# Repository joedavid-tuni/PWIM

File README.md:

## ELECTRONIC CONTROL OF HYRDRAULIC SYSTEMS

## Description of the Task

As mobile equipment becomes more technologically sophisticated, the need for electronic control of
hydraulic systems is growing.

Electronic components have become more reliable and rugged. They can now withstand the harsh
environmental conditions required for mobile equipment applications. Sophisticated electronic
controllers normally supply only low power control signals.

The goal of the project is to build an electronic driver circuit that compensates the stiction and
hysteresis of a hydraulic valve that makes their behaviour seem erratic and unpredictable. Once we
get over these issues we move on to implement a current sensing mechanism by which the current
in the solenoid circuit is prevented from fluctuating due to varying resistance from varying
temperatures of the coil. We as such are not interested in the position of the spool at any given
point in time but rather only to regulate the current.

## Table of Contents

- Terms of Reference
- Abstract
- Acknowledgement
- 1. Introduction
   - 1.1 Hydraulic Valve
      - 1.1.1 Introduction
      - 1.1.2 Working Principle
      - 1.1.3 Solenoid
      - 1.1.4 Characteristics of Solenoid Coil
   - 1.2 Methods for Proportional Control
      - 1.2.1 Using a potentiometer in Series with the Solenoid
      - 1.2.2 Pulse Width Modulation
      - 1.2.3 Problems associated with Proportional Control of Solenoids
   - 1.3 Solutions to Problems associated with Proportional Control – The Concept of Dither
      - 1.3.1 High frequency PWM
      - 1.3.2 Low frequency PWM
      - 1.3.3 Superimposing Low Frequency Dither on High Frequency Signal
- 2. Current Sensing
   - 2.1 INA219
   - 2.2 PID Algorithm
- 3. Project Work
   - 3.1 Major Hardware Components
   - 3.2 Software
      - 3.2.1 Simulation
      - 3.2.2 Programming IDE
      - 3.2.3 PCB Design Software
   - 3.3 Project Implementation
      - 3.3.1 Basic Circuit
      - 3.3.2 Calculating Inductance
      - 3.3.3 Dither
      - 3.3.4 Current Sensing
      - 3.3.5 Making the PCB
- 4. Project Setup
- 5. Conclusion
- 6. Project Resources
- 7. References
- APPENDIX A: I^2 C Communication Protocol
- APPENDIX B: Setting PWM Frequency on Arduino
- APPENDIX C: The PID Algorithm
- APPENDIX D: TROUBLESHOOTING
- Figure 1: Parts of the Hydraulic Valve List of Figures
- Figure 2: Internal cross section of the Hydraulic Valve
- Figure 3: Coil of Solenoid A energized
- Figure 4: Neutral Position of Valve Plunger
- Figure 5: Testing using mechanical override
- Figure 6: Cross-sectional sketch of Solenoid A of hydraulic valve
- Figure 7: Depiction of the magnetic field around solenoid
- Figure 8: Solenoid current characteristics
- Figure 9: Width of pulses at different duty cycles
- Figure 10: Duty cycle with respective current waveform
- Figure 11: A typical hysteresis curve in an electro hydraulic proportional valve
- Figure 12: Dither as a by-product of low frequency PWM
- Figure 13: Low Frequency Dither superimposed on high frequency PWM
- Figure 14: Functional block diagram of commercially available Solenoid Driver
- Figure 15: Dither Generating Circuitry of a commercially available driver
- Figure 16: Software Code for creating Dither
- Figure 17: Functional Block Diagram of INA219 Sensor
- Figure 18: LCD Display used in the project
- Figure 19: Screenshot of Multisim GUI
- Figure 20: Screenshot of Labcenter Proteus GUI
- Figure 21: Screenshot of Arduino IDE GUI
- Figure 22: Screenshot of Autodesk Eagle GUI
- Figure 23: An FET and a freewheeling diode used to drive the solenoid valve.
- Figure 24: Laboratory setup while calculating inductance
- Figure 25: Oscilloscope Screenshot at resonance
- Figure 26: Multisim simulation circuit
- Figure 27: Breadboard schematic
- Figure 28: General Schematic
- Figure 29: Simulated oscilloscope screenshot (Low frequency)
- Figure 30: Project Implementation waveform from the Arduino (Low frequency)
- Figure 31: Simulated oscilloscope screenshot (High frequency)
- Figure 32: Project Implementation waveform from the Arduino (High frequency)
- Figure 33:: Project Implementation of superimposed waveform from the Arduino.
- Figure 34: Breadboard schematic for current sensing
- Figure 35: Project implemented waveform from the Arduino with current sensing incorporated
- Figure 36: Schematic of Printed Circuit Board of Valve Driver Circuit
- Figure 37: Board Layout of Printed Circuit Board of Valve Driver Circuit
- Figure 38: 3D rendered images of designed Printed Circuit Board
- Figure 39: 3D rendered images of designed Printed Circuit Board
- Figure 40: 3D rendered images of designed Printed Circuit Board
- Figure 41: 3D rendered images of designed Printed Circuit Board
- Figure 42: Project Setup

## 1. Introduction

### 1.1 Hydraulic Valve

#### 1.1.1 Introduction

The Hydraulic Valve used for this Project is a bi-directional solenoid valve from BOSCH.

These are designed to perform any of three actions. They direct the flow of fluid in a hydraulic
system in a particular direction. They can halt or initiate the flow of fluid in a system. Directional
valves can also change the direction in which a fluid flows within a circuit. Various directional valves
are incorporated in hydraulic systems to enable proper flow of fluids. Spool valves in particular are
designed to block and allow the flow of fluid within a hydraulic system.

Parts of the Hydraulic Valve (as labelled in Figure 1)

1. 3 port/chamber system with spool guidance
2. Pressure tight solenoid
3. Optimized flow paths
4. Manual override with return spring

#### Figure 1 : Parts of the Hydraulic Valve

#### 1.1.2 Working Principle

#### Figure 2: Internal cross section of the Hydraulic Valve

The valve contains two coils on its either end and together with the valve tube that contains an  armature and a push pin make up what is known as a solenoid.

In the main body of the valve there are two springs that help return the spool when no solenoids are
energized. The lines with the gauges labelled A and B are the work ports that typically connect to a
hydraulic cylinder or a motor.

When Solenoid A of the valve is energized an electromagnetic field is created (Figure1). The field
pulls the armature in towards the centre of the winding which causes the armature to slide easily in
a tube that is internally lubricated with hydraulic oil. The armature moves the push pin and
ultimately the push pin moves the valve spool towards the right and now there will be a flow from
the pump directed to work port B. Likewise when Solenoid B is energized, the spool moves to the
left.

#### Figure 3: Coil of Solenoid A energized

Notice that when Solenoid A is energised the movement of the spool towards the right also causes
the pushpin and armature in Solenoid B is pushed to the right as well.

Also notice that in Figure 2 there is a gap present between the pushpin on the left side of the spool.
When Solenoid A is energized the armature and the push pin gets a running start against the spool
as the gap is closed.

When the solenoid returns to the neutral position after Solenoid A is energized the gap is present
with the Solenoid B. Whichever side of the valve has the pushpin gap has a slight force advantage
when that Solenoid is next energized (Figure 4 ).

#### Figure 4: Neutral Position of Valve Plunger

In order to help with troubleshooting and basic valve testing, the valve is provided with a mechanical
override (Figure 5), A mechanical override is simply a pin on the outside end of the valve tube in the
centre of the solenoid assembly that can be activated with a small screwdriver or hex key. Pushing
on the mechanical override is a simple way to find out if the internal parts of the valve is still free to
move and operating normally.

#### Figure 5: Testing using mechanical override

#### 1.1.3 Solenoid

The hydraulic solenoid valve as mentioned has two solenoids as actuators mounted on either ends
of the valve body. These linear solenoids are electromechanical devices which convert electrical
energy into a linear mechanical motion which is used to control the hydraulic system.
Figure 6 shows a cross sectional sketch of the electromagnetic solenoid hydraulic valve. The
solenoids consist of an electromagnetically inductive coil wound around a movable armature, or
plunger. The coil is shaped such that the armature can be moved in and out of its centre, altering the
coil’s inductance. The plunger provides mechanical force to activate the control mechanism, for
example opening and closing of a valve.

#### Figure 6: Cross-sectional sketch of Solenoid A of hydraulic valve

#### 1.1.4 Characteristics of Solenoid Coil

A main electrical characteristic of a solenoid is that of an inductor that opposes any change in
current. This characteristic is why current does not immediately reach a maximum level when a
solenoid is energized. Instead, the current rises at a steady rate until it is limited by the DC resistance
of the solenoid.

#### Figure 7: Depiction of the magnetic field around solenoid

An inductor (in this case a solenoid) stores energy in the form of a concentrated magnetic field.
Whenever current is present in a wire or conductor, a magnetic field, however small, is created
around the wire. With the wire wound into a coil, such as in the solenoid, the magnetic field
becomes very concentrated. This electromagnet can control a mechanical valve through an electrical
signal.

As soon as the solenoid is energized, the current increases, causing the magnetic field to expand
until it becomes strong enough to move the armature and the corresponding solenoid current is
known as IPEAK.

#### Figure 8: Solenoid current characteristics

The armature movement increases the concentration of the magnetic field as the armature’s own
magnetic mass moves farther into the magnetic field. Remember, a magnetic field changing in the
same direction of the current creating it induces an opposing voltage into the windings. Because the
magnetic field quickly expands when the armature strokes, the field causes a brief reduction in the
current through the solenoid windings till a minimum known as IVALLEY (Figure 8). Notice the
prominent dip in the rising portion of the current waveform.

After the armature strokes, the current continues on its normal upward path to its maximum level. A
typical current waveform in shown in Figure 8.

### 1.2 Methods for Proportional Control

When voltage is applied to a valve coil, the current flowing through it creates a magnetic field which
provides the force to shift the valve’s spool. The input voltage divided by the resistance of the coil
equals the current draw. This is very straightforward when used with on/off valves, but proportional
valves are only useful if the spool position can be precisely controlled by varying the input current.

#### 1.2.1 Using a potentiometer in Series with the Solenoid

A simple potentiometer can be used to vary the resistance, which then varies the input current. This
is an inefficient method of control, and is not practical when high currents are required. Also, when
an infinitely variable DC signal is used to operate a proportional valve solenoid, the output transistor
functions like a variable resistor. It drops the power supply voltage down to the level required by the
solenoid coil at a particular time. The full coil current, which may be several amps, needs to pass
through this output transistor. The result is that the transistor builds up heat which requires a large
heat sink to dissipate.

#### 1.2.2 Pulse Width Modulation

Pulse Width Modulation (PWM) is a control technique which can overcome the problems described
above. With PWM, the output transistor is used as an on/off switch, feeding the solenoid coil with a
series of on/off pulses at a constant voltage. The pulses are set at a constant frequency, typically 400
to 5000+ Hz. The signal level is determined by varying the duration of the “on” pulses relative to the
“off” pulses.

The advantage of this technique is that during the “off” pulse, the output transistor is not passing
any current, and during the “on” pulse, there is virtually no voltage drop across the transistor and
therefore very little heat is created. In practice, there will be a small voltage drop across the
transistor during the “on” pulses, and it takes a finite amount of time to switch on and off, so a small
amount of heat is created. However, the amount of heat is much smaller than would be produced by
a conventional DC output signal.

PWM has become the standard for all valve amplifiers in order to reduce amplifier size and power
waste. No modifications are required to the valve solenoid in order to use this technique.

PWM is an efficient way to control current to a proportional valve coil. It allows the use of
electronics for current regulation, dither, ramping, short circuit protection, and the elimination of
deadband.

**How PWM Works**

A PWM signal is not constant, it is on for a period of time and off for a period of time (see Figure 9 ).

#### Figure 9: Width of pulses at different duty cycles

The duty cycle “D” refers to the “on” portion of the cycle. The duty cycle can be anywhere from 0
(signal always off) to 1 (signal always on). A 50% “D” results in a perfect square wave.

Inductance is the characteristic of a circuit that opposes the starting, stopping or changing of current
flow. Inductance in an electrical system is similar to inertia in a mechanical system. Its effect is to
introduce a time lag into the duty cycle wave form. In theory, the wave form is perfectly rectangular,
rising immediately when current is applied, and falling immediately when current is withdrawn.
Because of the effects of inductance, the actual wave form rises and falls more gradually (see Figure
10 ).

#### Figure 10: Duty cycle with respective current waveform

At 25% signal, “D” is shorter than the time it takes the current to reach its maximum value. This
results in reduced current output to the valve coil, and therefore a reduced hydraulic output from
the valve. If the PWM frequency is low enough, the current will fall to zero during the off time. This
is described as “discontinuous current.”

#### 1.2.3 Problems associated with Proportional Control of Solenoids

There are two major problems that are associated with basic proportional control of solenoid.

1. Stiction

Stiction keeps the valve spool from moving when input signal changes are small. When the signal
finally becomes large enough to initiate movement, the spool will tend to overshoot the position
required for accurate control.

2. Hysteresis

#### Figure 11: A typical hysteresis curve in an electro hydraulic proportional valve

The spool movement in a proportional valve has to overcome some amount of spring force as well
as static friction when the input signal is applied. These forces produce an effect known as
hysteresis. Additionally, the solenoid has to overcome the magnetic hysteresis due to the cyclic
magnetization and demagnetization of the solenoid core. The spool movement in response to the
increasing input signal is not the same as the spool movement created in response to the decreasing
input signal. Hysteresis as shown in the figure above is defined as the difference in the spool position
produced by a particular input signal when it is increasing and then decreasing.

Stiction and hysteresis can make the behaviour of a hydraulic proportional valve seem erratic and
unpredictable. In the following sections, we will see how to overcome these problems.

### 1.3 Solutions to Problems associated with Proportional Control – The Concept of Dither

Dither is a rapid, small movement of the spool around the desired position. It is intended to keep the
spool moving to avoid stiction and average-out hysteresis. Dither amplitude must be **large enough
and the frequency slow enough for the spool to respond, and yet amplitude small and frequency
fast enough to avoid creating a noticeable pulsation in the hydraulic output of the valve.** Dither is
caused by coil current “ripples”—current variations around the desired control signal value. Due to
inertia, the valve spool will follow low frequency ripples better than it will follow high frequency
ripples. The amplitude of the ripples determines if, or how far, the spool will move at a given
frequency.

#### 1.3.1 High frequency PWM

The solenoid valves are very often operated by means of PWM signals at a frequency that is high for
the solenoid valve, for example at l KHZ, in the linear or analog range. The armature of the solenoid
valve cannot synchronously follow this high control frequency in mechanical terms and assumes an
intermediate position.

#### 1.3.2 Low frequency PWM

Previously these problems Were solved in that the frequency of the control signal has been reduced
to such an extent, for example between 70 - 300 HZ, that the armature can still just about follow and
in the intermediate position or central position is preferably deflected only minimally. This results in
oscillation of the armature, and of the valve connected thereto, about the intermediate position at
low amplitude which is conventionally called dither oscillation (dither signal). This dither oscillation is
desired in principle since the friction resistances at the moving parts of the solenoid valve may be
reduced thereby.

However, it is very difficult to stipulate an optimally constant dither signal amplitude **since the
dither signal depends on the PWM frequency and on the pulse-duty factor (duty cycle)** and
therefore on the coil current flowing in the solenoid valve. With this method, it is therefore **not
possible for the dither signal to form a constant amplitude since the PWM frequency has to be
continuously adjusted as a function of the stipulated desired current value and in the process the
amplitude and the frequency of the dither signal change accordingly.**

#### Figure 12: Dither as a by-product of low frequency PWM

#### 1.3.3 Superimposing Low Frequency Dither on High Frequency Signal

A further solution for said problems consists in a low-frequency dither signal being superimposed on
the high frequency of the PWM signal by amplitude modulation. This allows the user to
**independently control** amplitude and frequency of the **solenoid current** and the **dither**. The dither
will therefore be constant for any current level, and its frequency and amplitude can be set by the
user to optimize the function of the particular hydraulic valve. This will be necessary as different
valves from different manufacturers would have different spool dynamics (inertia due to different
size, for example).

#### Figure 13: Low Frequency Dither superimposed on high frequency PWM

The dither is specified by its frequency (Hz) and peak-to-peak current. The dither amplitude is usually
adjustable from 0 to 10% of the rated maximum current of the solenoid.

It is to note that, if the dither frequency is in the range of the control frequency, undesirable low-
frequency beating of the magnetic current can occur. Even the hydraulic system may be damaged
thereby. The beating results because the dither frequency cannot be synchronized with the control
frequency.

**Hardware Techniques**

Most solenoid valve drivers make use of a separate dither generating circuitry and combines it with
the main PWM signal using op-amps. The functional block diagram of one such driver is as shown in
the figure below:

#### Figure 14: Functional block diagram of commercially available Solenoid Driver

A dither generating circuit of a commercially available solenoid driver is shown below. This is capable
of generating triangular and square wave dither.

#### Figure 15: Dither Generating Circuitry of a commercially available driver

Working principle:

The dither generator consists of a comparator stage (A1A), amplitude limiting stages (A1C/D2 AND
A1D/D1) and an integrating amplifier stage (A1B). In the beginning, A1A will attempt to go to
positive or negative saturation. However, the peak voltage will be restricted by D1/A1D or D2/A1C.
A1B ramps up or down, as whatever the case maybe, until the output voltage is sufficient to cause
the feedback voltage at the comparator (through voltage divider R8, R11) to change polarity. At this
point, the polarity of A1A changes and A1B ramp in the opposite direction. This way, the dither
signal is generated.

Solutions of this nature are cost-intensive.

**Software Technique**

For the context of the project, we focus only on
superimposing the dither on main PWM signal. As
such, the requirements are basic and we do not need
sophisticated electronics for the purpose. All the
hardware needed would be the basic hardware for
the PWM switching of the solenoid and the dither can
be implemented without using the dither circuitry buy
by rather manipulating the switching hardware
through the software. This section is a description of
how it is done.

#### Figure 16: Software Code for creating Dither

Using software, the microcontroller is programmed so that the duty cycle of the PWM is periodically
oscillated about its set setpoint, by the dither amplitude which in “duty-cycle language” is in effect a
small finite amount of pulse-duty factor. This in effect causes an extended and thereafter a
shortened PWM signal cyclically which emulates dither. This way, the pulse-duty factor is changed
by the desired amplitude of the dither signal exactly every consequent cycle.

A constant amplitude for the dither signal may advantageously be formed thereby, so the armature
of the solenoid valve always oscillates about its central position with identical excursions, without
the control frequency of the PWM signal being able to have an adverse effect. The resulting reduced
friction resistance therefore allows the position of the armature to be advantageously adjusted and
controlled much more accurately as discussed earlier

The low frequency of the dither signal means that the oscillation of the solenoid valve armature can
be individually adjusted to the type of solenoid valve being used, so, compared with the known
hardware solution, a high level of flexibility results because the adaptation to other types of solenoid
valve can take place by way of a simple calibration process by changing a value in the code that the
microcontroller uses to generate the dither. It is also cost efficient in terms of the components used
as the dither circuitry is now replaced by software code.

## 2. Current Sensing

As mentioned in the previous section, the armature of a solenoid provides a mechanical force to
activate the control mechanism. The force applied to the armature is proportional to the coil’s
change in inductance with respect to the armature’s change in position. The electromagnetic force
of a solenoid directly relates to the current. Traditionally, a voltage drive powers the solenoid coils;
Therefore, the coil consumes a continuous power. A negative effect of this power consumption is
the heating of the coil. The coil temperature is a result of many factors: ambient temperature, self-
heating due to the coil’s power consumption (V × I), heating induced by the contact system, and
other heat sources such as components in the vicinity of the relay. Due to coil heating, the coil
resistance increases. The resistance at elevated temperature is expressed by Equation:

where

- RCoil_20°C is the 20°C value for resistance
- kR_T is the thermal coefficient of copper (= 0.00404 per °C) (1)

Typically given in the datasheet of a solenoid coil, RCoil_20°C can calculate the worst-case coil
resistance at high temperatures.

To compensate for temperature induced changes, we have to implement some sort of current
sensing algorithm which essentially is a current feedback. This allows the solenoid current to be
proportional to the input signal voltage, and independent of the solenoid resistance. Power supply
voltage must be sufficient to overcome the increased or decreased resistance

### 2.1 INA219

The current sensor used for the project is the INA219.

The two analog inputs to the INA219, IN+ and IN–, connect to a shunt resistor in the bus of interest.
The INA219 is typically powered by a separate supply from 3 to 5.5 V. The INA219 senses the small
op across the shunt for shunt voltage, and senses the voltage with respect to ground from IN– for
the bus voltage. Figure 13 shows this operation

#### Figure 17: Functional Block Diagram of INA219 Sensor

### 2.2 PID Algorithm

The PID Controller is implemented to achieve the current sensing functionality. See APPENDIX C: The
PID Algorithm to see the details of the PID Algorithm.

The PID algorithm consists of three basic coefficients; proportional, integral and derivative which are
varied to get optimal response. The basic idea behind a PID controller is to read the values from the
current sensor, then compute the desired actuator output by calculating proportional, integral, and
derivative responses and summing those three components to compute the output.

**Proportional Response:** The proportional component depends only on the difference between the
set point and the process variable. This difference is referred to as the Error term. The proportional
gain (Kp) determines the ratio of output response to the error signal. Increasing the proportional
gain will increase the speed of the control system response. However, if the proportional gain is too
large, the process variable will begin to oscillate. If Kp is increased further, the oscillations will
become larger and the system will become unstable and may even oscillate out of control.

**Integral Response:** The integral component sums the error term over time. The result is that even a
small error term will cause the integral component to increase slowly. The integral response will
continually increase over time unless the error is zero, so the effect is to drive the Steady-State error
to zero. Steady-State error is the final difference between the process variable and set point. A
phenomenon called integral windup results when integral action saturates a controller without the
controller driving the error signal toward zero.

**Derivative Response:** The derivative component causes the output to decrease if the process
variable is increasing rapidly. The derivative response is proportional to the rate of change of the
process variable. Increasing the derivative time (Td) parameter will cause the control system to react
more strongly to changes in the error term and will increase the speed of the overall control system
response. Most practical control systems use very small derivative time (Td), because the Derivative
Response is highly sensitive to noise in the process variable signal. If the sensor feedback signal is
noisy or if the control loop rate is too slow, the derivative response can make the control system
unstable

**Tuning**

The method used for tuning the PID Controller in this project is the “trial and error” method.

In this method, the I and D terms are set to zero first and the proportional gain is increased until the
output of the loop oscillates. As one increases the proportional gain, the system becomes faster, but
care must be taken not make the system unstable.

Once P has been set to obtain a desired fast response, the integral term is increased to stop the
oscillations. The integral term reduces the steady state error, but increases overshoot. Some amount
of overshoot is always necessary for a fast system so that it could respond to changes immediately.
The integral term is tweaked to achieve a minimal steady state error.

Once the P and I have been set to get the desired fast control system with minimal steady state
error, the derivative term is increased until the loop is acceptably quick to its set point. Increasing
derivative term decreases overshoot and yields higher gain with stability but would cause the system
to be highly sensitive to noise.

## 3. Project Work

### 3.1 Major Hardware Components

**Arduino**

The Arduino Uno is a microcontroller board based on the
ATmega328. Arduino is an open-source, prototyping
platform. The Arduino Uno has 14 digital input/output
pins (of which 6 can be used as PWM outputs), 6 analog
inputs, a 16 MHz crystal oscillator, a USB connection, a
power jack, an ICSP header, and a reset button. It
contains everything needed to support the
microcontroller; simply connect it to a computer with a
USB cable or power it with a AC-to-DC adapter or battery
to get started.

Features of the Arduino UNO:

- Microcontroller: ATmega328
- Operating Voltage: 5V
- Input Voltage (recommended): 7-12V
- Input Voltage (limits): 6-20V
- Digital I/O Pins: 14 (of which 6 provide PWM output)
- Analog Input Pins: 6
- DC Current per I/O Pin: 40 mA
- DC Current for 3.3V Pin: 50 mA
- Flash Memory: 32 KB of which 0.5 KB used by bootloader
- SRAM: 2 KB (ATmega328)
- EEPROM: 1 KB (ATmega328)

## • Clock Speed: 16 MHz

We use the Arduino to create the appropriate PWM signals for controlling the voltage to the
solenoid and to implement the algorithm for current sensing.

**Bidirectional Hydraulic Vale**

Manufacturer: Bosch Rexroth (BRH)

Part No.: 0810091203

Solenoid Specs:

Rating: 24V, 1.4A

**Power Supply**

Specs:

Rating: 24V,2.5A

**INA219, Bidirectional Current/Power Monitor with I2C Interface**

The INA219 is current shunt and power monitor with and I^2 C
interface. This along with the fact that it could be wired on the high
side were the prime reasons the device was selected to be used with
the I2C compatible Arduino.

The device is capable of monitoring both shunt voltage and the bus
supply voltage. The device uses a 3-5V supply, drawing a maximum of 1 mA of supply current and
operates from -40°C to 125°C.

**16x4 Liquid Crystal Display.**

A 16x4 LCD Display is used to display the circuit parameters such as duty cycle, current, etc. real
time.

The parameters on Display are:

Line 1: Duty cycle (Range: 0- 100 , from setpoint) Voltage: Voltage of the Solenoid Circuit
Line 2: I1 : Current sensed by the I2: Expected Current from duty cycle
current sensor (Feedback for PID)
Line 3: Power: VI Power Dissipated in the Solenoid Circuit
Line 4: PID constants (Kp, Ki, Kd)

#### Figure 18: LCD Display used in the project

**Other Electrical Components**

```
Device Part No. Rating Quantity Remarks
FET IRF3205PbF VDSS = 55V, ID = 110A (n-Ch) 1 Switching Device
Capacitor .001K 63 100nF 1 Noise Filter
Resistor - 12Ω 1 Current Limiter
Diode 1N5400 3A, Rectifier Diode 1 Freewheeling Diode
Potentiometer/
Joystick
```
- 10KΩ 1 Input to the System

### 3.2 Software

#### 3.2.1 Simulation

National Instruments, Multisim v12.0 (used for simulating electrical characteristics)

#### Figure 19: Screenshot of Multisim GUI

LabCenter, Proteus 8 (used for simulating arduino microcontroller (with code) with electrical circuit)

#### Figure 20: Screenshot of Labcenter Proteus GUI

#### 3.2.2 Programming IDE

##### ARDUINO IDE

#### Figure 21: Screenshot of Arduino IDE GUI

#### 3.2.3 PCB Design Software

#### Figure 22: Screenshot of Autodesk Eagle GUI

### 3.3 Project Implementation

Before the implementation, the circuit needs to be simulated to study the response of the
circuit beforehand so that time is no wasted during implementation stage. An added benefit would
be familiar results and pre-known reasoning during the implementation phase. As mentioned in the
earlier sections we use MultiSim v12.0 and Proteus 8.0 for simulations. Proteus simulations were
made to study the behaviour while designing the project work and its observations are not recorded
here.

#### 3.3.1 Basic Circuit

Driving a solenoid is a rather simple task with very little need for sophisticated electronics. Still, the
basics of inductive load driving must be taken care of if we are to safely actuate this load. These
requisites are:

- A large enough voltage must be applied across the winding in order to supply a current with
    enough magnitude as to push/pull the piston.
- The switch or power stage must be sized according to the dc current we expect to see
    flowing across the solenoid winding.
- An alternate path must be applied to take care of the flowing current once the switching
    element is disabled.

A normal MOSFET requires around 10V applied to the Base pin to fully turn on. Because driving
anything above 5V with an Arduino requires using a level-shifter or amplifier, we use what is called a
logic-level MOSFET (IRF 3205) for direct integration. A logic-level MOSFET can be turned on with a 5v
“logic level” signal, which can be easily interfaced to the Arduino.

If a normal MOSFET with an amplified input from the Arduino is used, care must be taken not to
exceed the maximum gate-to-source voltages. If the limit is exceeded for even a second, it can
destroy the MOSFET, so care should be taken to work within the voltage limits of the MOSFET. The
maximum voltage that can be applied to the gate pin is listed in the datasheet as the “Gate to Source
Voltage” or “Vgs” —this number is usually between 18vdc and 25vdc.

For the IRF 3205 we the maximum Vgs is 20V, so it is safe as the Arduino cannot prover over 5V with
direct integration.

The typical solenoid driver circuit is a single FET transistor with enough current handling capability to
drive the load (IRF 3205), and a freewheeling diode which is forward biased when the FET is
disabled. When the FET is enabled, it sinks all the current needed to polarize the inductor. When the
transistor is disabled, the current flowing through the inductance must be allowed to decay down to
zero. The freewheeling diode is forward biased taking this current and avoiding damage to the
power FET. Figure 1 9 shows the two possible states a solenoid will experience as it is energized

#### Figure 23: An FET and a freewheeling diode used to drive the solenoid valve.

Note that a H-bridge circuit is not used as it’s not a bistable solenoid where the direction of motion
is according to the magnetic field polarity. Hence the direction of current flow is not relevant and
use of an H-bridge would be an overkill as it would need 4 FETs as opposed to one in this case.

All information required to begin simulations is present except one, the inductance of the solenoid
of the hydraulic valve. This was neither found in the product datasheet nor was available with the
Bosch Customer Service personnel on contacting them. So, a basic test is carried out to approximate
the inductance of the solenoid.

#### 3.3.2 Calculating Inductance

To calculate the inductance, connect the solenoid of the hydraulic valve in parallel with a capacitor
to form a tank circuit. Use a function generator to run a small current through the circuit and an
oscilloscope to view the waveform across the solenoid. Next, sweep the function generator
frequency from its lowest top highest range. In this range, the tank's resonant frequency is where
the oscilloscope registers the largest waveform.

#### Figure 24: Laboratory setup while calculating inductance

Resonant Frequency of LC tank circuit is given by the formula:

##### 푓=

##### 1

##### 2 휋√퐿퐶

Equation 1

From the equation 1 the inductance can be found, L, as:

##### 퐿=

##### 1

##### ( 2 휋푓)^2 .퐶

Equation 2

Resonance was found to obtained at around 150Hz using
a capacitor of 10μF.

Substituting in Equation 2, the inductance,

```
L= 0.10554 H or 105.54mH
```
#### 3.3.3 Dither

Now, that the inductance of the solenoid is established, it is simulated in softwares. Next,
simulations at both higher and lower frequencies is carried out and the observations are recorded
below.

**Simulation Circuit**

The circuit built is shown in the figure below.

As can be seen the **voltage across the solenoid is connected to channel A** and **the current in the
solenoid is connected to channel B** of the oscilloscope.

#### Figure 25: Oscilloscope Screenshot at resonance

#### Figure 26: Multisim simulation circuit

**Arduino Valve Driver Circuit**

#### Figure 27: Breadboard schematic

## Figure 28: General Schematic

The PWM frequency on most pins is ~490 Hz. However, it's ~980 Hz for pins 5 and 6 on the Uno. To
obtain lower frequencies a deeper understanding on the hardware implementation of the ATMEL
328p Microprocessor that the Arduino uses is necessary.

See APPENDIX B: Setting PWM Frequency on the Arduino to see how a frequency different from that
of the default frequency was obtained.

Also see APPENDIX D: Troubleshooting to see how to eliminate noises in the analog input

The waveforms from the scope are shown in the figure below.

**Low Frequency Dither Observations**

(refer Section 2.3.2 for literature)

Frequency: ( 60 Hz) and PWM with
duty cycle: 80%

**Simulation Results:**

## Figure 29: Simulated oscilloscope screenshot (Low frequency)

As described in Section 2.3.2, low frequency PWM generates dither (current ripple) as a by-product
of the PWM process. The PWM frequency is low enough so that the current has time to decay
before the next rise begins.

**Project Implementation Results**

## Figure 30: Project Implementation waveform from the Arduino (Low frequency)

The above is a plot of instantaneous values of the current (Y-axis) vs time (x-axis) that that micro-
controller records. The blue is the expected current value at 80% duty cycle whereas the redline is
the current values sensed by the sensor in the feedback circuit. It is observed that the frequency of
the PWM is low enough that it reduces to 0 at moments. This is in line with what was expected and
as shown in the simulations

**Valve Behaviour**

As the duty cycle was increased, the plunger of the solenoid began to vibrate with larger amplitude
and finally actuated. This was as expected as mentioned in the Section 2.3.2. Changing the PWM
frequency will allow adjusting the dither, but the amplitude and frequency of the dither cannot be
set independently.

**Results from Test Bench.**

Due to large hysteresis of the solenoid used in the test bench, the dither could be observed in the
initial stages for a brief amount of time but it quickly actuated.

**High Frequency Dither Observations**

(refer Section 2.3.1 for literature)

**Simulation Results:**

Frequency: ( 490 Hz – Arduino Default frequency) and PWM with
duty cycle: 80%

## Figure 31: Simulated oscilloscope screenshot (High frequency)

Here, it is clear that the frequency of the PWM signal is high enough that it does not let the current
to a minimum zero value.

**Valve Behaviour**

The armature of the solenoid valve cannot synchronously follow the current in mechanical terms
and assumes an intermediate position. With a pulse duty factor of 50% of the PWM signal this then
corresponds to the central position of the valve “half open”. But this as discussed in Section 2 .3.1
will be subject to problems of stiction and thereby hysteresis due to lack of dither oscillation.

**Project Implementation Results**

There were no significant dither observations, as expected. The high frequency did not allow the
plunger dither oscillations.

## Figure 32: Project Implementation waveform from the Arduino (High frequency)

The blue is the expected current value at 80% duty cycle whereas the redline is the current values
sensed by the sensor in the feedback circuit. The frequency of the PWM is high enough to produce a
continuous current.

```
-- Input
-- Setpoint
```

**Superimposing Low Frequency Dither on High Frequency Signal**

(refer Section 2.3.3 for literature)

This is obtained in the software implementation by periodically varying the duty cycle.

**The PWM frequency runs at a high frequency, while
the duty cycle oscillation along with a delay in
between produces the effect of low frequency dither.**

**Valve behaviour**

This causes just enough oscillation of the solenoid
plunger, not to keep it stationary as well not to
produce considerable variation in the plunger
displacement.

## Figure 33:: Project Implementation of superimposed waveform from the Arduino.

Here the “dither_time” variable is set to 10ms so 1 complete cycle of the dither wave takes
approximately 20ms. Hence the **dither frequency is 50Hz**

The blue is the expected current value at 80% duty cycle whereas the redline is the current values
sensed by the sensor in the feedback circuit.

At the moment, there isn’t any feedback which is why there is considerable steady state error.

```
-- Input
-- Setpoint
```

#### 3.3.4 Current Sensing

**Introduction**

Here the objective is to implement a PID algorithm, that inputs feedback from a current sensor. As
discussed in Section 3 the objective is to make sure that for a given setpoint from the input joystick,
the output must be the same at all times, irrespective of the varying ambient temperature due
varying weather conditions

**Circuit Diagram**

The circuit is rigged up as per the following diagram,

```
Current sensing
```
## Figure 34: Breadboard schematic for current sensing

**Software Code**

The code begins with the necessary pre-processor directives. They are invoked by the compiler to
process the class definitions before compilation.

Next, initialize objects of these classes, to use them throughout the code.

Initialize Variables for use

Setup Function, that runs once when the Arduino runs the program.

The setup function is used to setup the parameters of the instances of class objects initialized earlier.
This includes the LCD, PID, Current Sensor and the Arduino GPIO Pins.

**Loop Function**

This function is the main function and runs every cycle continuously

See APPENDIX D: Troubleshooting to set a PWM frequency on the fly with carrying setpoint.

**PID Tuning**

See APPENDIX C: The PID Algorithm to see the details of the PID Algorithm.

The procedures taken during tuning were as discussed in Section 3.2.

On starting the tuning the proportional constant the oscillations were already high. Hence it was
decided to keep the Kp parameter near zero or zero. The parameters suitable for the project were
found to be **Kp = 0, Ki = 10 and Kd=0.**

**Project Implementation Results**

## Figure 35: Project implemented waveform from the Arduino with current sensing incorporated

It can be observed that as the duty cycle of the PWM output is varied (blue line), output (green line)
varies almost instantaneously so that the input (current in the solenoid coil) closely follows the
setpoint.

When the current in the solenoid of the hydraulic valve reduces due to the increase in the resistance
the PID controller automatically adjusts the output to achieve the desired current level.

```
-- Output
-- Input
-- Setpoint
```

#### 3.3.5 Making the PCB

Once the objectives of the project have been achieved, it is made permanent by transferring the
breadboard to a Printed Circuit Board.

The software Eagle, from Autodesk is used for the purpose to sketch the PCB.

Features of the PCB

1. Besides the circuit already discussed, an additional power circuit is added that is used to
    power the PCB and provide power to the INA219 sensor. It provides a regulated output of 5V
    (4.8V-5.2V) from an external input voltage (5V-18V) through a DC Barrel Connector (2.1mm
    centre positive).
2. 4 Pairs of 5V power supply headers are provided to power auxiliary devices such as an LCD
    or a variable analog input such as a potentiometer or a joystick. Please note that the current
    sensor is powered from within the PCB and a separate connection is not required.

**Schematic:**

## Figure 36: Schematic of Printed Circuit Board of Valve Driver Circuit

**Board View:**

## Figure 37: Board Layout of Printed Circuit Board of Valve Driver Circuit

##### 43

**Rendering**

## Figure 38: 3D rendered images of designed Printed Circuit Board

## Figure 39: 3D rendered images of designed Printed Circuit Board

## 4. Project Setup

## Figure 42: Project Setup

## 5. Conclusion

The report starts with literature discussing certain important aspects in the electronic control of
hydraulic systems.

Next, the solenoid valve used in the project was characterised by conducting basic tests on it initially
to determine its inductance as it was not provided in the accompanying datasheet. This information
was used to simulate models in softwares Multisim and Proteus to study the Low Frequency and
High Frequency PWM response with reference to the topics discussed in the literature. Its behaviour
during the simulations were studied and a temporary test circuit was built on a breadboard and the
implementation results were compared with that of the simulation.

A software based technique for determining a control signal for a solenoid valve is next discussed,
the control signal being a PWM signal on which a frequency of a dither signal is superimposed and
having a frequency such that the spool of the solenoid valve assumes an intermediate position
between which the armature oscillates with slight excursions at the frequency of the dither signal.

Upon successful implementation of dither, a current sensing circuit was built using a fine tuned PID
algorithm. Finally, after running successful tests, a PCB for the prototype was designed.

## 6. Project Resources

All the files used in this project develop are available online at the GitHub repositories with links
given below.

Arduino Sketch: https://github.com/joedavid91/PWIM/tree/master/Arduino%20Code/PWIM

Simulation Files: https://github.com/joedavid91/PWIM/tree/master/Simulation%20Files

Fritzing Sketches: https://github.com/joedavid91/PWIM/tree/master/Fritzing%20Sketches

Eagle PCB Files: https://github.com/joedavid91/PWIM/tree/master/Eagle%20PCB%20Files

Links to Videos:

Low Frequency Dither: https://youtu.be/j71BZkSpgNY

Laboratory Setup with current sensing: https://youtu.be/wHQWNnsTs0Q

Real time PID Plot with current sensing: https://youtu.be/J_p4m4B9xHs

## 7. References

##### [1] “ ELECTRONIC CONTROL OF HYDRAULIC SYSTEMS”

[http://www.hydraforce.com](http://www.hydraforce.com)

##### [2] “FLOW AND DIRECTIONAL CONTROL VALVES”

[http://www.lunchboxsessions.com](http://www.lunchboxsessions.com)

[3] _“Detection of Plunger Movement in DC Solenoids”_ Manu Balakrishnan, Navaneeth Kumar N
Texas Instruments

[4] _“Method and Device for determining a PWM Signal on which a dither frequency is
superimposed in order to control a solenoid” Jose Cruz Kissler Fernandez, Thomas Rohrl_

[5] _“Driving solenoid coils efficiently in switchgear applications_ ” Sanjay Pithadia, Texas
Instruments

[6] “ _Arduino Robotics”_ John-David Warren, Josh Adams and Harald Molle

[7] “ _Secrets of Arduino PWM”_ Ken Shirriff’s blog

## APPENDIX A: I^2 C Communication Protocol

The INA219 offers compatibility with both I2C and SMBus interfaces of which the I2C will be used as
it is compatible with the Arduino. Two bidirectional lines, SCL and SDA, connect the INA219 to the
bus. Both SCL and SDA are open-drain connections meaning that they can pull the corresponding
signal line low, but cannot drive it high. Thus, there can be no bus contention where one device is
trying to drive the line high while another tries to pull it low, eliminating the potential for damage to
the drivers or excessive power dissipation in the system. Each signal line has a pull-up resistor on it,
to restore the signal to high when no device is asserting it low.

The device that initiates the transfer, the Arduino, is called a master, and the devices controlled by
the master are slaves. The Arduino generates the serial clock (SCL), controls the bus access, and
generates START and STOP conditions.

Messages are broken up into two types of frame: an address frame, where the master indicates the
slave to which the message is being sent, and one or more data frames, which are 8-bit data
messages passed from master to slave or vice versa. Data is placed on the SDA line after SCL goes
low, and is sampled after the SCL line goes high. The time between clock edge and data read/write is
defined by the devices on the bus and will vary from chip to chip.

Start Condition

To initiate the address frame, the master device leaves SCL high and pulls SDA low. This puts all slave
devices on notice that a transmission is about to start. If two master devices wish to take ownership
of the bus at one time, whichever device pulls SDA low first wins the race and gains control of the
bus.

Address Frame

The address frame is always first in any new communication sequence. For a 7-bit address, the
address is clocked out most significant bit (MSB) first, followed by a R/W bit indicating whether this
is a read (1) or write (0) operation.

The 9th bit of the frame is the NACK/ACK bit. This is the case for all frames (data or address). Once
the first 8 bits of the frame are sent, the receiving device is given control over SDA. If the receiving
device does not pull the SDA line low before the 9th clock pulse, it can be inferred that the receiving
device either did not receive the data or did not know how to parse the message. In that case, the
exchange halts, and it’s up to the master of the system to decide how to proceed.

Data Frames

After the address frame has been sent, data can begin being transmitted. The master will simply
continue generating clock pulses at a regular interval, and the data will be placed on SDA by either
the master or the slave, depending on whether the R/W bit indicated a read or write operation. The
number of data frames is arbitrary, and most slave devices will auto-increment the internal register,
meaning that subsequent reads or writes will come from the next register in line.

Stop condition

Once all the data frames have been sent, the master will generate a stop condition. Stop conditions
are defined by a 0->1 (low to high) transition on SDA after a 0 - >1 transition on SCL, with SCL
remaining high. During normal data writing operation, the value on SDA should not change when SCL
is high, to avoid false stop conditions.

## APPENDIX B: Setting PWM Frequency on Arduino.......................................................................

The idea here is not to provide a detailed overview of how the processor manages the register, but
only to provide enough information to understand the code in the context of the project.

The ATmega328P has three timers known as Timer 0, Timer 1, and Timer 2. Each timer has two
outputs compare registers that control the PWM width for the timer's two outputs: when the timer
reaches the compare register value, the corresponding output is toggled. The two outputs for each
timer will normally have the same frequency, but can have different duty cycles (depending on the
respective output compare register).

Each of the timers has a prescaler that generates the timer clock by dividing the system clock by a
prescale factor such as 1, 8, 64, 256, or 1024. The Arduino has a system clock of 16MHz and the
timer clock frequency will be the system clock frequency divided by the prescale factor. Note that
Timer 2 has a different set of prescale values from the other timers.

The timers are complicated by several different modes. The main PWM modes are "Fast PWM" and
"Phase-correct PWM" of which the Fast PWM will be used and is described below

Let’s take Timer 1 for example

The Timer/Counter Control Registers TCCR1A and TCCR1B hold the main control bits for the timer.
(Note that TCCR1A and TCCR1B do not correspond to the outputs A and B.) These registers hold
several groups of bits:

- Waveform Generation Mode bits (WGM): these control the overall mode of the timer.

(These bits are split between TCCR1A and TCCR1B.)

- Clock Select bits (CS): these control the clock prescaler
- Compare Match Output A Mode bits (COM1A): these enable/disable/invert output A
- Compare Match Output B Mode bits (COM1B): these enable/disable/invert output B

The Output Compare Registers OCR1A and OCR1B set the levels at which outputs A and B will be
affected. When the timer value matches the register value, the corresponding output will be
modified as specified by the mode.

**Base frequencies:**

The base frequency for pins 3, 9, 10, and 11 is 31250 Hz.

The base frequency for pins 5 and 6 is 62500 Hz.

**Divisors:**

The divisors available on pins 5, 6, 9 and 10 are: 1, 8, 64, 256, and 1024 which are selected by the
mode values and are in hexadecimal format.

The divisors available on pins 3 and 11 are: 1, 8, 32, 64,128, 256, and 1024 which are selected by the
mode values and are in hexadecimal format.

PWM frequencies are tied together in pairs of pins. If one in a pair is changed, the other is also
changed to match:

Pins 5 and 6 are paired on timer0

Pins 9 and 10 are paired on timer1

Pins 3 and 11 are paired on timer2

Below is a code for a function that accepts the Arduino output pin number and the divisor as
arguments which it uses to attain varying frequencies on the Arduino (UNO)

The resulting frequency is equal to the base frequency divided by the given divisor:

## APPENDIX C: The PID Algorithm

Please note that sections of the code that are irrelevant, of negligible importance or self-explanatory
are omitted to keep this section concise.

**The PID class Constructor**

The PID class constructor is used to intialize an instance / obect of the class PID. All the information
regarding the PID object are to be passed as parameters to the constructor. The Input, Output and
the Setpoint variables are pointers, and a reference to these pointer variables are usedwhile creating
the class object as shown below :

The constructor is also used to assign the PID tuning parameters Kp,Ki and Kd using the SetTunings
function (shown in code above). The **step time** is set to **0.1s or 100ms**

The SetOutputLimits function sets the maximum outout of the PID controller. This is necessary as its
intended to control the PWM ouptut of the arduino which is in the range 0-255 as its 8-bit. Without
this function the PID would increase the output beyond 255 and there would be an overflow as the
PWM value is only 8bit.

Lines 67 - 69 of the compute funciton ( code in next page ) ensure that the PID is called only at a
regular interval, based on a **predetermined step time, i.e 100ms**. Once the PID is evaluated at a
constant interval, the derivative and integral calculations can also be simpligfied. As a result of this,
the SampleTimeInSec variable appears in the SetTunings function (code in previous page), which are
multiplied or divided while setting the tuning parameters itself. because it is now known that it’s
going to be the same time between samples,it is unecessary to constantly multiply by time change
which is why time doesn’t appear in the setTunings function. The result is mathematically
equivalent, but more efficient as it saves a multiplication and a division every time the PID is
evaluated

**Compute Function.**

This is where the all the PID computation takes place.

This function should be called every time "void loop()" function of the arduino executes. the
function will decide for itself whether a new pid Output needs to be computed, i.e whether the time
since the previous computation is greater than the constant sample interval defined in the
constructor. It returns true when the output is computed, false when nothing has been done.

**Lines 71- 74** Computes the working error variables.

**Lines 76 and 77** Clamps the Output to its maximum (255) and minimum (0) values respectievely and
make sure there is no over flow.

**Lines 8 0 - 82** , computes the proportional on error output term and adds it to the Final Output on
**lines 8 5**

**Lines 9 7 - 89** , clamps the output to either the maximum or mimnimum values as earlier. This is
necessary to be taken care of at each stage as the variables in the arduino code are referenced as
pointers and any momentary overflow of the PWM register bits can adversely affect the stability of
the system.

**Lines 92 & 93** are used to store the current input time for use in the next computation cycle.

## APPENDIX D: TROUBLESHOOTING

This Section presents few challenges that were faced during the project implementation and how
they were overcome.

**Heating of the MOSFET**

MOSFETs have tiny capacitors attached to their gate pins to maintain the voltage present at the
gate. The capacitor charge enables the MOSFET to stay activated, even after the power is removed
from the gate pin. Each time the MOSFET is switched, the gate capacitor must fully charge and
discharge its current.

As the PWM frequency that is applied to the MOSFET switch increases, the time allowed for the gate
capacitor to charge and discharge decreases. As this happens, the gate-capacitor will require more
current from the driver to fully charge and discharge in the shorter amount of time. If the current
available from the driver is not sufficient to fully charge and discharge between switching cycles, the
gate will be left in a partially conducting state, which can result in excess heating.

Saying that a MOSFET needs a lot of available current to switch quickly might seem puzzling, because
MOSFETs require a specific voltage to turn on and typically very little current. Although the 40mA
that the Arduino PWM output pin can supply is plenty of current to fully switch a MOSFET on or off
slowly, it is not enough to fully charge and discharge the MOSFETs gate-capacitor at high PWM
frequencies where the MOSFET capacitor needs to be fully charged and drained 10,000 (10Khz) to
32,000 (32Khz) times per second!

A solution to this would be using a MOSFET driver IC (specialized signal-buffer) drive the MOSFET
switch because it can provide much more current during each switching cycle than the Arduino is
capable of.

It is also a good idea to ensure that the gate is forced to its off state by using a “pull-down” resistor
to drain the capacitor when not actively powered by the Arduino. Using a 10kOhm pull-down
resistor from the gate pin to the source pin (gate to GND on n-channel, gate to VCC on p-channel)
will be sufficient to keep the MOSFET turned off when not in use.

**Having different frequencies at different duty cycles on the fly**

The code used in the project section sets the main PWM (not dither) of the Arduino in the setup function
and remains the same throughout the execution of the program. Sometimes it may be required that this
PWM signal be changed on the fly with different PWM frequencies at different setpoints. This may be
due an increased stiction at some point or strange hysteresis patterns obtained during the spool
movement. It might be unwieldy to call the setPwmFrequency() method every time this needs to be
done. Rather a more efficient method is presented below.

Here Timer1 is used, which is 16bit, and allows for a number to be stored in a register (ICR1), and the
frequency is calculated based on that number. This gives me outputs on pins 9 and 10.
The number can be any value from 0 – 65535 (size = 16 bits).
The output frequency is given by the formula:

```
표푢푡푝푢푡 푓푟푒푞푢푒푛푐푦=
```
##### 푓

##### 2 푥푁푥푇푂푃

Where f = main clock (16MHz)
N = pre-scalar (see APPENDIX B)

TOP = the value in ICR 1
Based on the values of ICR1 from 1 to 65535 we get a frequency range from 15Hz to 1MHz.
So for example:
ICR1 = 10,000 gives f = 100Hz
ICR1 = 5000 gives f = 200Hz
ICR1 = 2500 gives f = 500Hz and so on..

To do this, the timer is configured to run in phase and frequency correct mode, and can set it to
either inverting or non-inverting mode. The pre-scalar should also be selected.

These configurations are done by adjusting Timer1 registers TCCR1A and TCCR1B.

First thing to adjust is choosing Phase and Frequency correct mode in invert or non-invert mode.

Second thing to adjust is PWM, Phase and Frequency correct mode, with the TOP value determined
by the ICR1 register, which is what determines the PWM Frequency.

The last thing to do is to adjust the pre-scalar.

This is done by choosing the right modes from the above table. As discussed earlier, we shall be
using mode which divides the main clock by 8.

**Smoothing Arduino Analog Input**

While reading the analog input from the joystick or potentiometer it is most likely that the input
behaves like the red line in the below picture. This also partially applies to the analog input of the
feedback sensor

As can be seen, if the fluctuating setpoint drives the PID algorithm crazy. First of all, it’s imperative to
check whether the Arduino and the rest of the circuit have a common ground. This is necessary. A
couple of additional measures were taken to fix this problem

1. Adding a filter capacitor from the analog input pin to ground as shown in Figure 27

2. Using an averaging algorithm. In this project, a basic averaging algorithm is used using a for-
    loop as it was found to suffice. There are however there are more robust algorithms such as
    the moving average or weighted average, the exponential moving average etc.

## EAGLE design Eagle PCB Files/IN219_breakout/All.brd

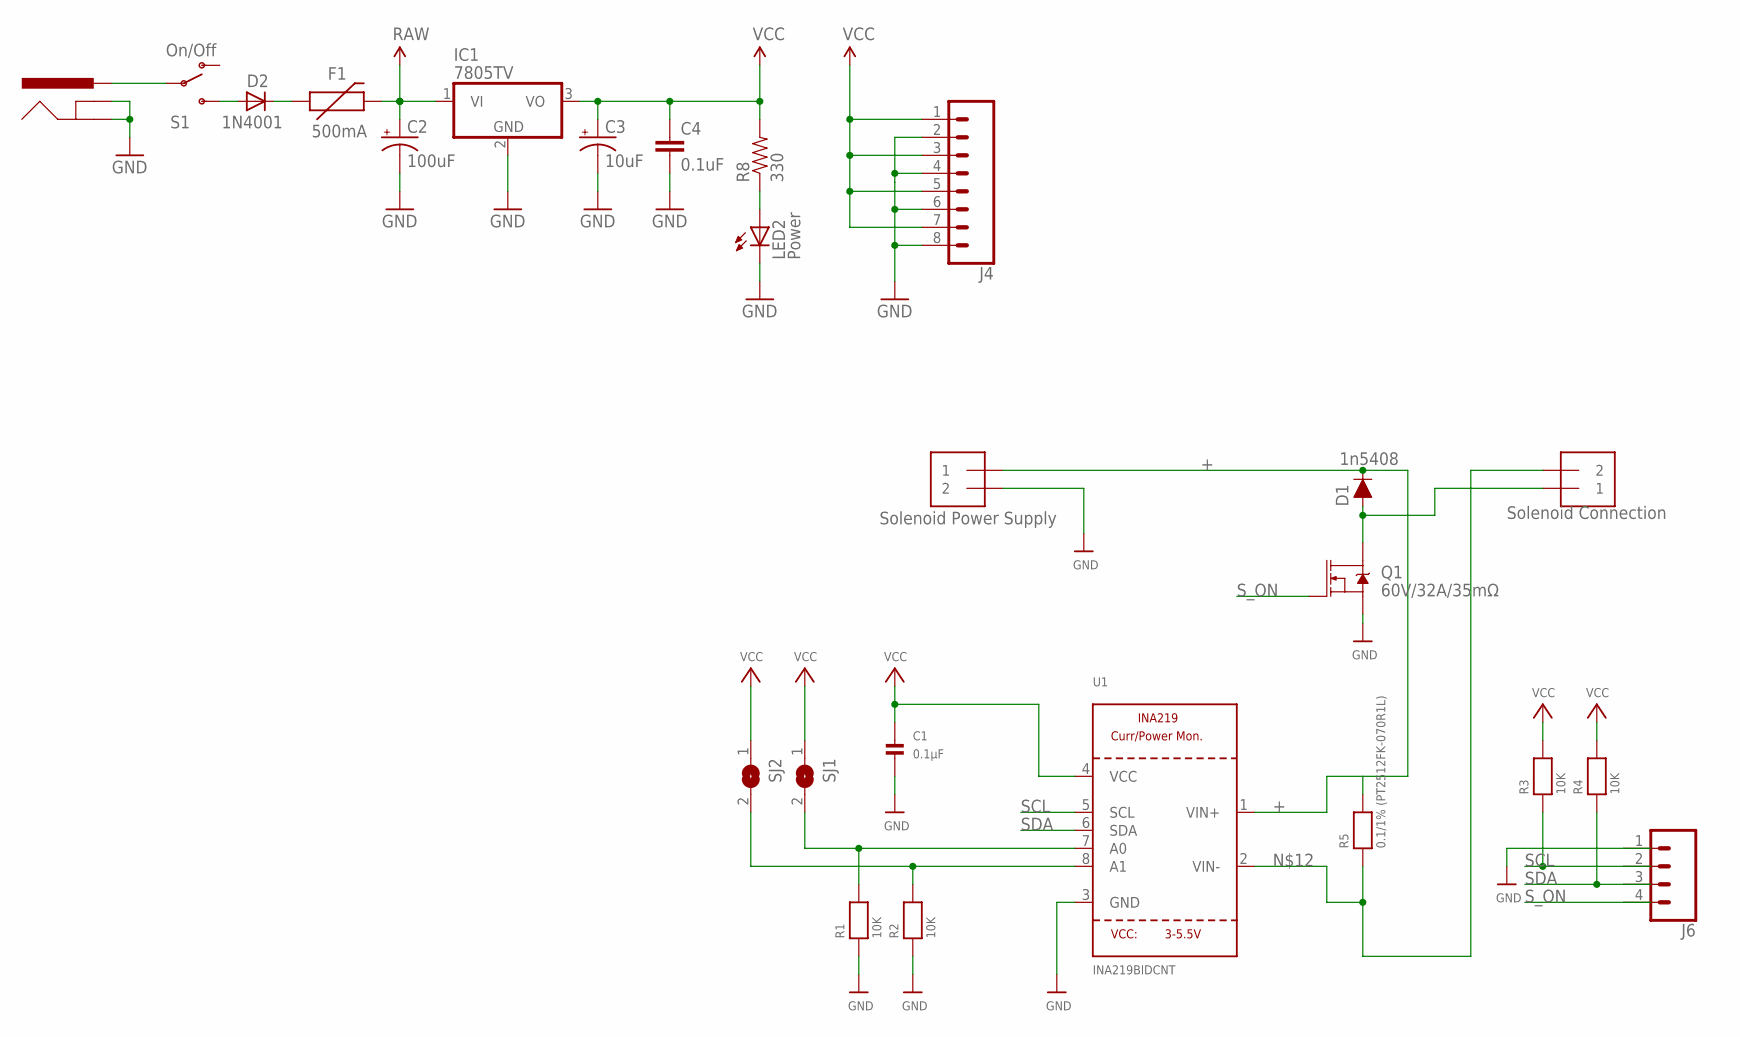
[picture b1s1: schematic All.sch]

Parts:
C1: 0.1µF; 0805
C2: 100uF; CPOL-RADIAL-100UF-25V
C3: 10uF; CPOL-RADIAL-10UF-25V
C4: 0.1uF; CAP-PTH-SMALL2
D1: DIODE-1N4148
D2: 1N4001; DIODE-0.4
F1: 500mA; PTC
IC1: 7805TV; TO220V
J1: POWER_JACKPTH; POWER_JACK_PTH
J2, J3: TERMBLOCK_1X2-3.5MM; 1X2-3.5MM
J4: CONN_08"; 1X08
J6: CONN_04; 1X04
LED2: Power; LED5MM
Q1: 60V/32A/35mΩ; TO220V
R1, R2, R3, R4: 10K; 0805
R5: 0.1/1% (PT2512FK-070R1L); 2512
R8: 330; AXIAL-0.3
S1: On/Off; SWITCH-SPST
SJ1, SJ2: SOLDERJUMPERREFLOW_NOPASTE; SOLDERJUMPER_REFLOW_NOPASTE
U1: INA219BIDCNT; SOT23-8

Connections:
+: D1.C, J2.1, R5.2, U1.1 (VIN+)
GND: C1.2, C2.2 (-), C3.2 (-), C4.2, IC1.2 (GND), J1.GND, J1.GNDBREAK, J2.2, J4.2, J4.4, J4.6, J4.8, J6.1, LED2.K (C), Q1.3 (S), R1.1, R2.1, U1.3 (GND)
unnamed: R2.2, SJ2.2, U1.8 (A1)
unnamed: R1.2, SJ1.2, U1.7 (A0)
unnamed: D1.A, J3.1, Q1.2 (D)
unnamed: J1.PWR, S1.2
unnamed: LED2.A, R8.P$1 (1)
unnamed: D2.C, F1.P$1 (1)
unnamed: D2.A, S1.3 (S)
unnamed: J3.2, R5.1, U1.2 (VIN-)
RAW: C2.1 (+), F1.P$2 (2), IC1.1 (VI)
SCL: J6.2, R3.1, U1.5 (SCL)
SDA: J6.3, R4.1, U1.6 (SDA)
S_ON: J6.4, Q1.1 (G)
VCC: C1.1, C3.1 (+), C4.1, IC1.3 (VO), J4.1, J4.3, J4.5, J4.7, R3.2, R4.2, R8.P$2 (2), SJ1.1, SJ2.1, U1.4 (VCC)

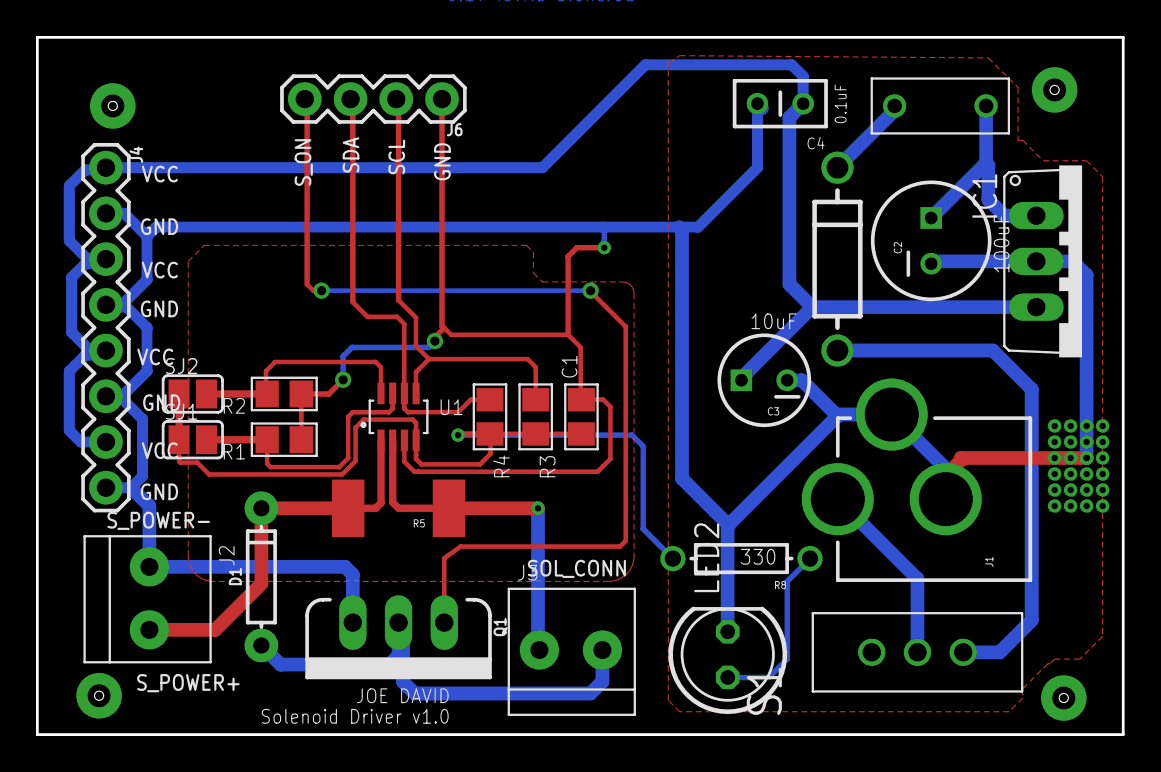
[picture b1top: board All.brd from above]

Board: 2 copper layers, 60.3 x 38.7 mm, 25 parts (0 on the bottom side), 15 nets.

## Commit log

2018-02-20 initial readme commit

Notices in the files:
parts and their libraries:
SparkFun-DiscreteSemi: Licensing: Creative Commons ShareAlike 4.0 International - https://creativecommons.org/licenses/by-sa/4.0
